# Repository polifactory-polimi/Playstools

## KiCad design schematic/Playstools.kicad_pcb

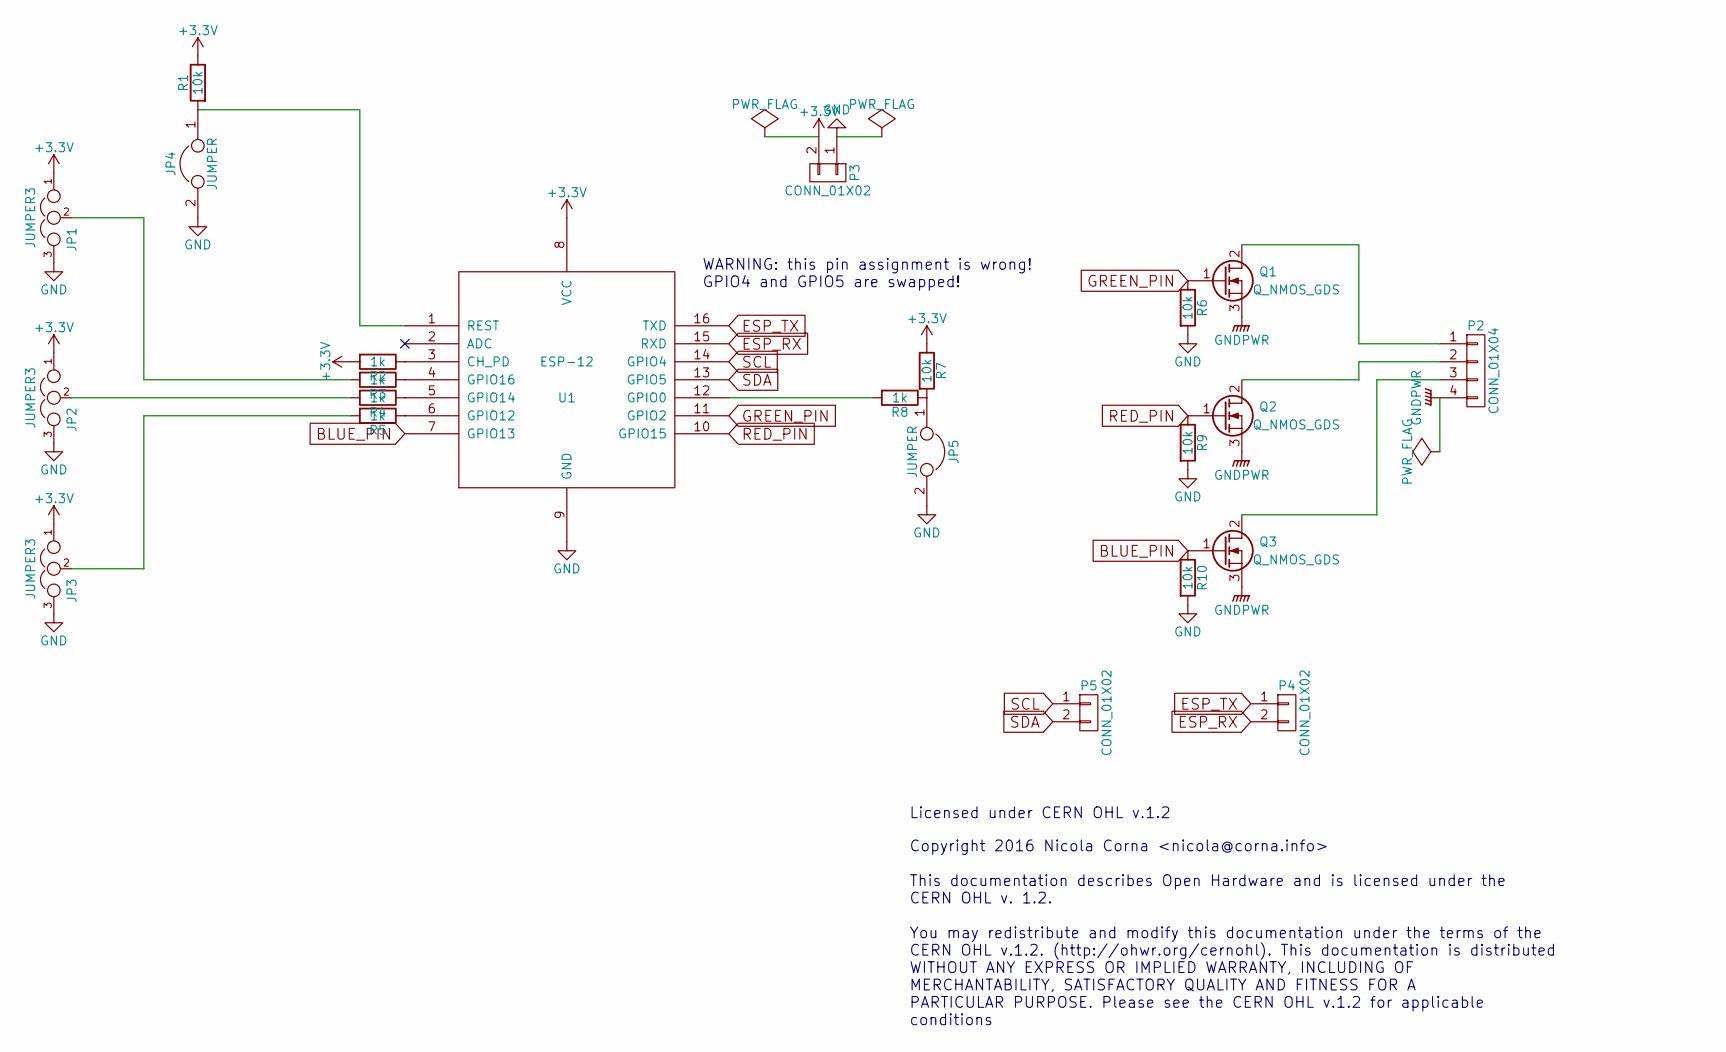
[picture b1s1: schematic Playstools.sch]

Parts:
JP1, JP2, JP3: JUMPER3; S_JUMPER_3
JP4, JP5: JUMPER; Pin_Header_Straight_1x02
P2: CONN_01X04; Pin_Header_Straight_1x04
P3, P4, P5: CONN_01X02; Pin_Header_Straight_1x02
Q1, Q2, Q3: Q_NMOS_GDS; SOT-404
R1, R6, R7, R9, R10: 10k; R_1206
R2, R3, R4, R5, R8: 1k; R_1206
U1: ESP-12

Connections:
+3V3: JP1.1, JP2.1, JP3.1, P3.2, R1.1, R2.2, R7.1, U1.8 (VCC)
BLUE_PIN: Q3.1 (G), R10.1, U1.7 (GPIO13)
ESP_RX: P4.2, U1.15 (RXD)
ESP_TX: P4.1, U1.16 (TXD)
GND: JP1.3, JP2.3, JP3.3, JP4.2, JP5.2, P3.1, R6.2, R9.2, R10.2, U1.9 (GND)
GNDPWR: P2.4, Q1.3 (S), Q2.3 (S), Q3.3 (S)
GREEN_PIN: Q1.1 (G), R6.1, U1.11 (GPIO2)
unnamed: JP1.2, R3.2
unnamed: JP2.2, R4.2
unnamed: JP3.2, R5.2
unnamed: JP4.1, R1.2, U1.1 (REST)
unnamed: JP5.1, R7.2, R8.1
unnamed: P2.1, Q1.2 (D)
unnamed: P2.2, Q2.2 (D)
unnamed: P2.3, Q3.2 (D)
unnamed: R2.1, U1.3 (CH_PD)
unnamed: R3.1, U1.4 (GPIO16)
unnamed: R4.1, U1.5 (GPIO14)
unnamed: R5.1, U1.6 (GPIO12)
unnamed: R8.2, U1.12 (GPIO0)
RED_PIN: Q2.1 (G), R9.1, U1.10 (GPIO15)
SCL: P5.1, U1.14 (GPIO4)
SDA: P5.2, U1.13 (GPIO5)

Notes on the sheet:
Copyright 2016 Nicola Corna <nicola@corna.info> This documentation describes Open Hardware and is licensed under the CERN OHL v. 1.2. You may redistribute and modify this documentation under the terms of the CERN OHL v.1.2. (http://ohwr.org/cernohl). This documentation is distributed WITHOUT ANY EX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
Licensed under CERN OHL v.1.2
WARNING: this pin assignment is wrong! GPIO4 and GPIO5 are swapped!

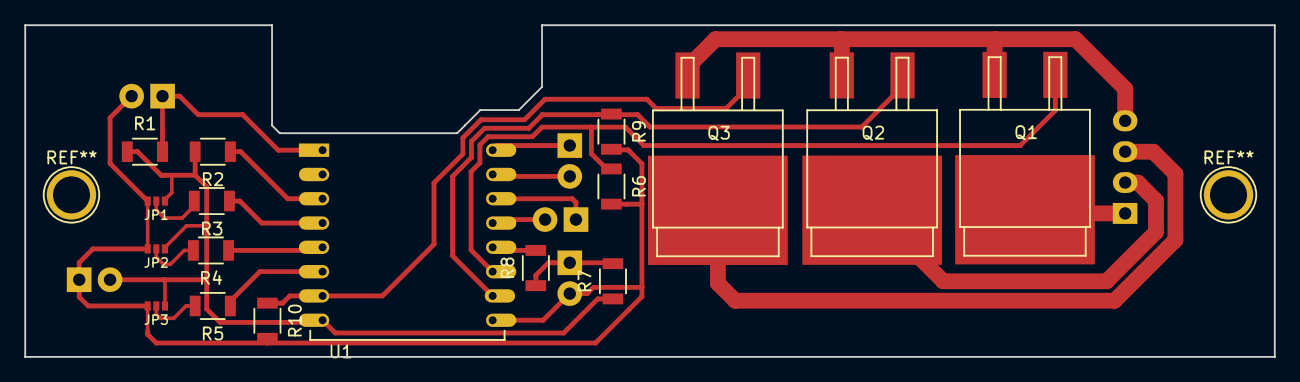
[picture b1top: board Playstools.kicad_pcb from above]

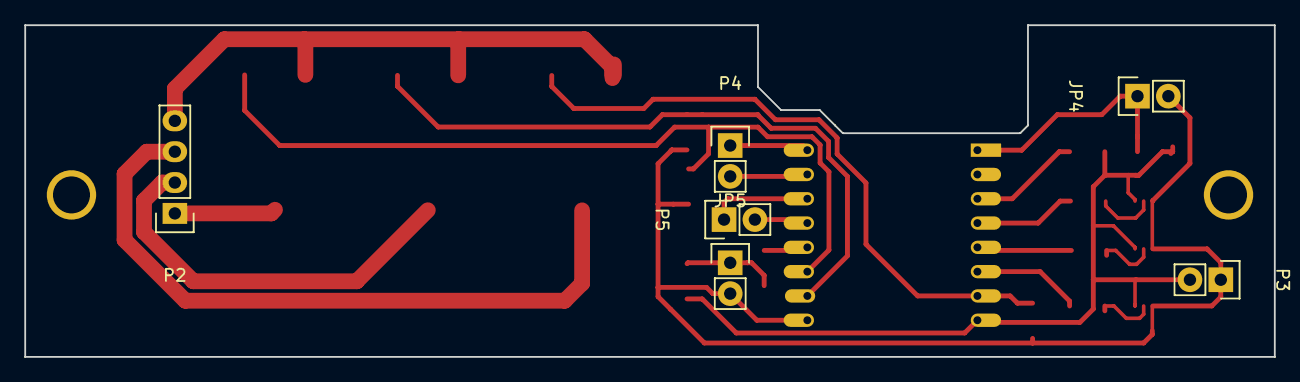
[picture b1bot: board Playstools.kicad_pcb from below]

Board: 2 copper layers, 102.9 x 27.3 mm, 23 parts (6 on the bottom side), 23 nets.

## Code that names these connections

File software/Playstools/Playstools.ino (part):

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const uint8_t addr_pin_1 = 14;
const uint8_t addr_pin_0 = 12;

const uint8_t red_pin = 15;
const uint8_t green_pin = 2;
const uint8_t blue_pin = 13;

const uint8_t sda_pin = 4;
const uint8_t scl_pin = 5;
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
const RGB blackred[] = { RGB(0, 0, 0), RGB(255, 0, 0) };

const RGB rgb_pins = { .red = red_pin, .green = green_pin, .blue = blue_pin };

RGBFader *fader;
Ticker nextStepTicker;
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  pinMode(addr_pin_1, INPUT);
  pinMode(addr_pin_2, INPUT);
  
  pinMode(red_pin, OUTPUT);
  pinMode(green_pin, OUTPUT);
  pinMode(blue_pin, OUTPUT);

  analogWriteFreq(150);

  analogWrite(red_pin, 0);
  analogWrite(green_pin, 0);
  analogWrite(blue_pin, 0);

  Serial.begin(115200);

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
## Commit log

2016-04-15 Fix stools colors

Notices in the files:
software/Playstools/Playstools.ino:
Copyright (C) 2016 Nicola Corna <nicola@corna.info>
Playstools is free software: you can redistribute it and/or modify
it under the terms of the GNU General Public License as published by
the Free Software Foundation, either version 3 of the License, or
(at your option) any later version.
